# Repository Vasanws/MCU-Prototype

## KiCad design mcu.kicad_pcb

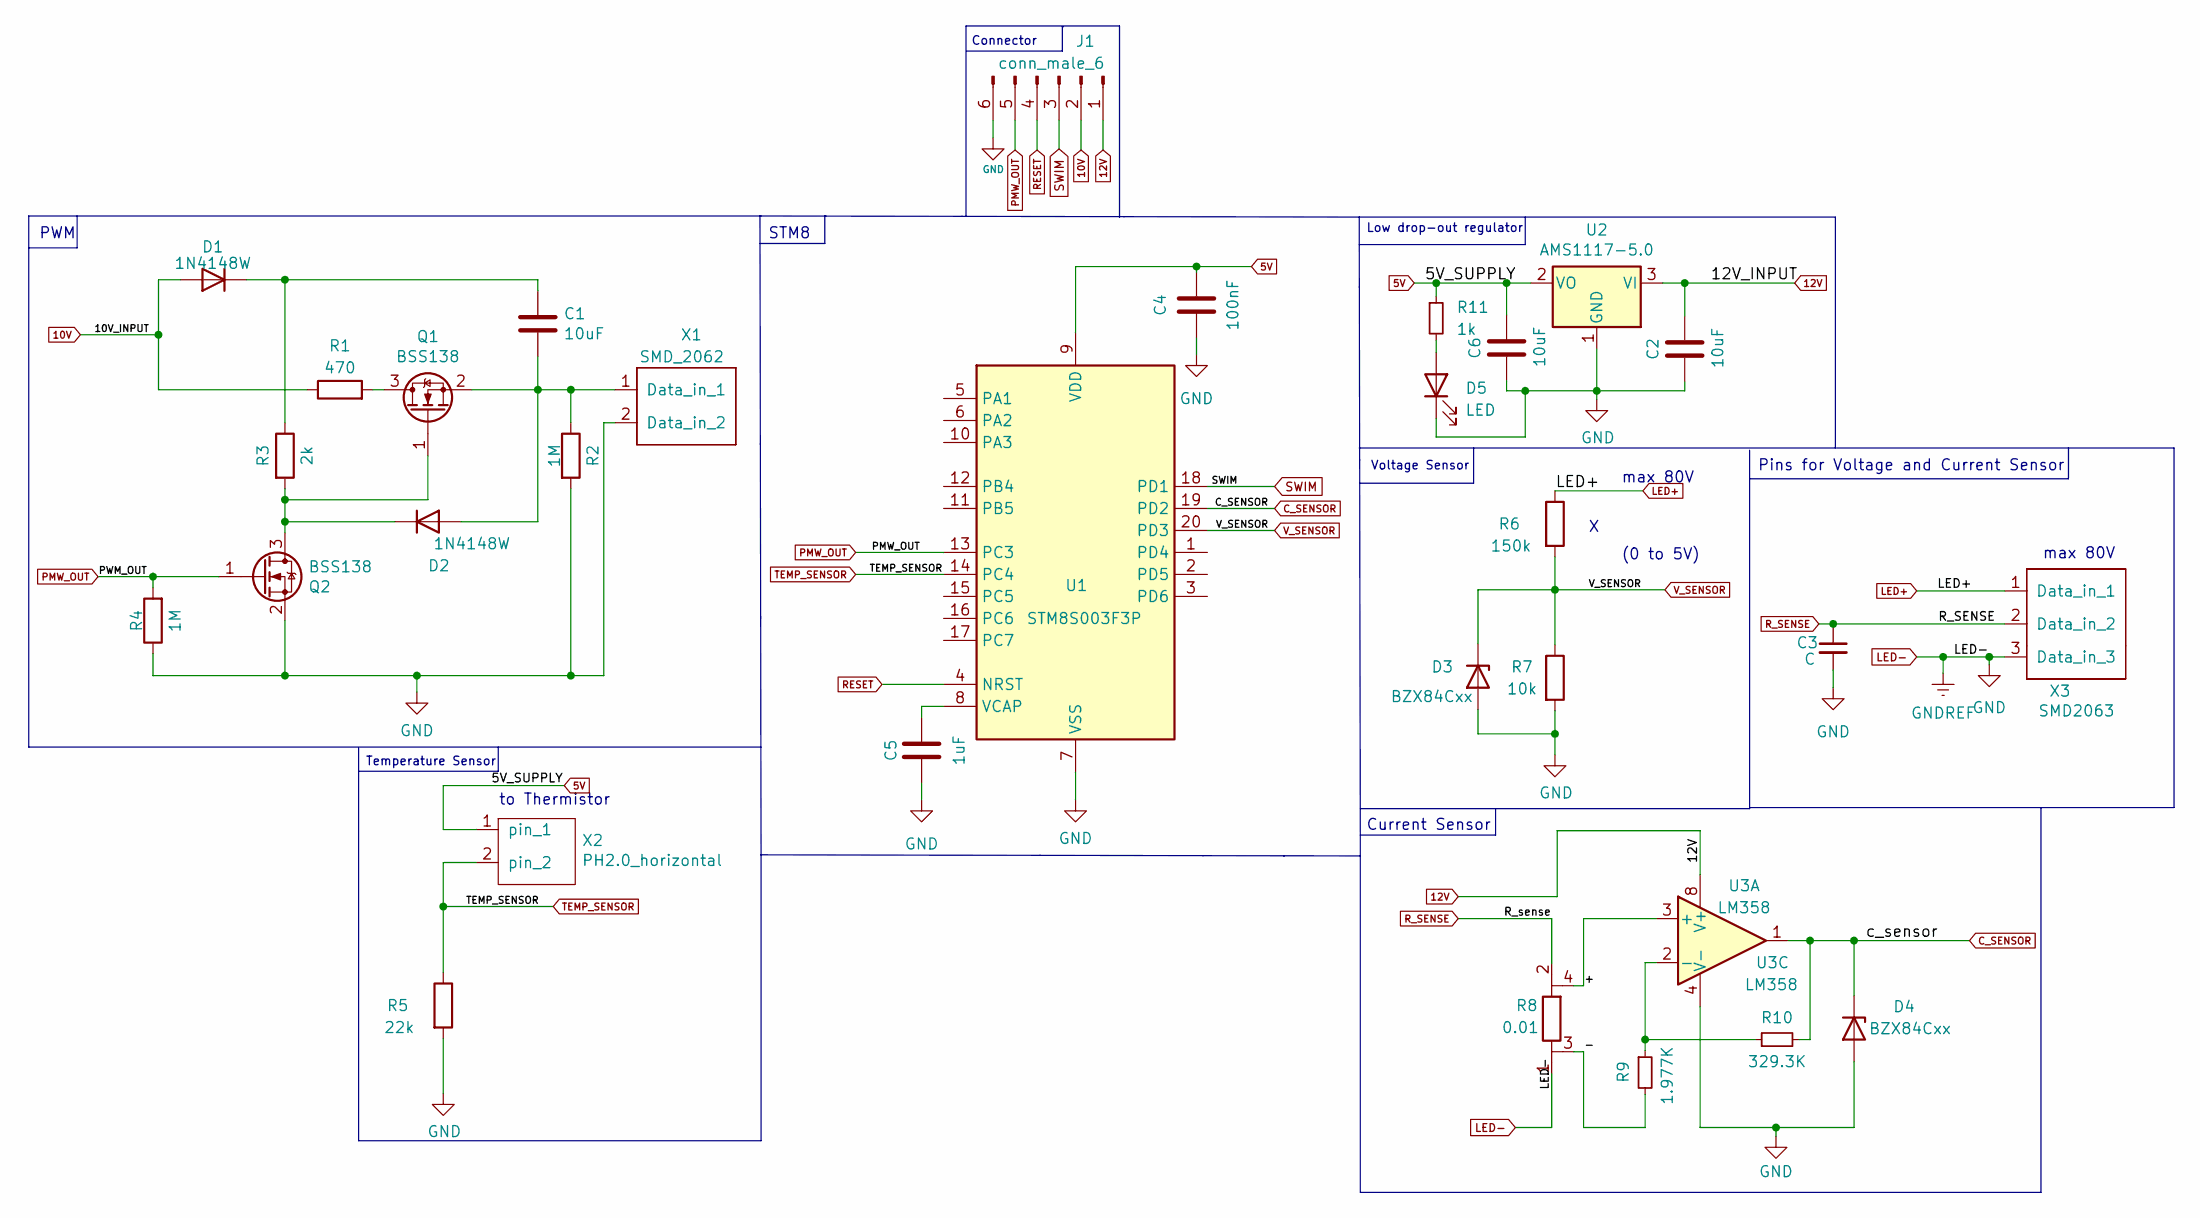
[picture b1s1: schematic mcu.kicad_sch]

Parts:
C1, C2, C6: 10uF; C_0805_2012Metric
C3: C; C_0805_2012Metric_Pad1.18x1.45mm_HandSolder
C4: 100nF; C_0805_2012Metric
C5: 1uF; C_0805_2012Metric
D1, D2: 1N4148W; D_SOD-123
D3, D4: BZX84Cxx; SOT-23
D5: LED; LED_0603_1608Metric
J1: conn_male_6; PinHeader_1x06_P2.54mm_Vertical
Q1, Q2: BSS138; SOT-23
R1: 470; R_0805_2012Metric
R2, R4: 1M; R_0805_2012Metric
R3: 2k; R_0805_2012Metric
R5: 22k; R_0805_2012Metric
R6: 150k; R_0805_2012Metric
R7: 10k; R_0805_2012Metric
R8: 0.01; R_1210_RSENSEMetric
R9: 1.977K; R_0805_2012Metric_Pad1.20x1.40mm_HandSolder
R10: 329.3K; R_0805_2012Metric_Pad1.20x1.40mm_HandSolder
R11: 1k; R_0805_2012Metric
U1: STM8S003F3P; TSSOP-20_4.4x6.5mm_P0.65mm
U2: AMS1117-5.0; SOT-223-3_TabPin2
U3: LM358; SOIC-8_3.9x4.9mm_P1.27mm
X1: SMD_2062; LEDSMD2062
X2: PH2.0_horizontal; JST_PH_S2B-PH-SM4-TB_1x02-1MP_P2.00mm_Horizontal
X3: SMD2063

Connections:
5V: C4.1, C6.1, R11.1, U1.9 (VDD), U2.2 (VO), X2.1 (pin)
10V: D1.2 (A), J1.2, R1.1
12V: C2.1, J1.1, U2.3 (VI), U3.8 (V+)
/+: R8.4, U3.3 (+)
/-: R8.3, R9.2
C_SENSOR: D4.3 (K), R10.2, U1.19 (PD2), U3.1
LED+: R6.1, X3.1 (Data_in)
LED-: C2.2, C3.2, C4.2, C5.1, C6.2, D3.1 (A), D4.1 (A), D5.1 (K), J1.6, Q2.2 (S), R2.2, R4.1, R5.2, R7.2, R8.1, U1.7 (VSS), U2.1 (GND), U3.4 (V-), X1.2 (Data_in), X3.3 (Data_in)
unnamed: C1.1, D1.1 (K), R3.1
unnamed: C1.2, D2.2 (A), Q1.2 (S), R2.1, X1.1 (Data_in)
unnamed: C5.2, U1.8 (VCAP)
unnamed: D2.1 (K), Q1.1 (G), Q2.3 (D), R3.2
unnamed: D5.2 (A), R11.2
unnamed: Q1.3 (D), R1.2
unnamed: R9.1, R10.1, U3.2 (-)
PMW_OUT: J1.5, Q2.1 (G), R4.2, U1.13 (PC3)
RESET: J1.4, U1.4 (NRST)
R_SENSE: C3.1, R8.2, X3.2 (Data_in)
SWIM: J1.3, U1.18 (PD1)
TEMP_SENSOR: R5.1, U1.14 (PC4), X2.2 (pin)
V_SENSOR: D3.3 (K), R6.2, R7.1, U1.20 (PD3)

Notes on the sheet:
STM8
(0 to 5V)
PWM
Temperature Sensor
Voltage Sensor
max 80V
Connector
to Thermistor
Low drop-out regulator
Current Sensor
Pins for Voltage and Current Sensor

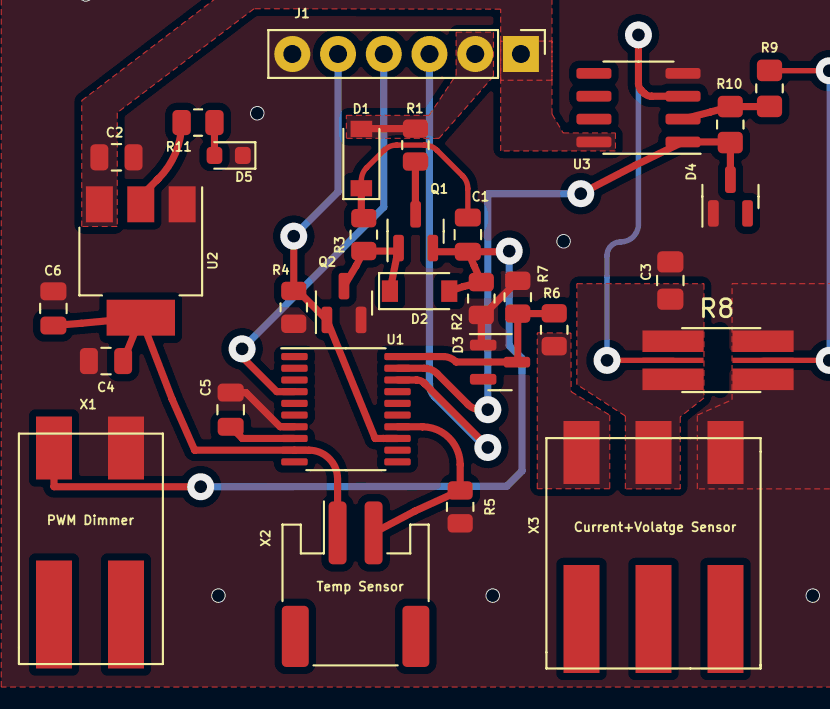
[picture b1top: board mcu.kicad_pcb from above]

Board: 2 copper layers, 31 parts (0 on the bottom side), 21 nets.

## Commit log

2022-08-01 mcuprototype
